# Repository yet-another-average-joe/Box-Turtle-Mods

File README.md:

# Box-Turtle-Mods
Box Turtle mods based on 78mm-wide trays

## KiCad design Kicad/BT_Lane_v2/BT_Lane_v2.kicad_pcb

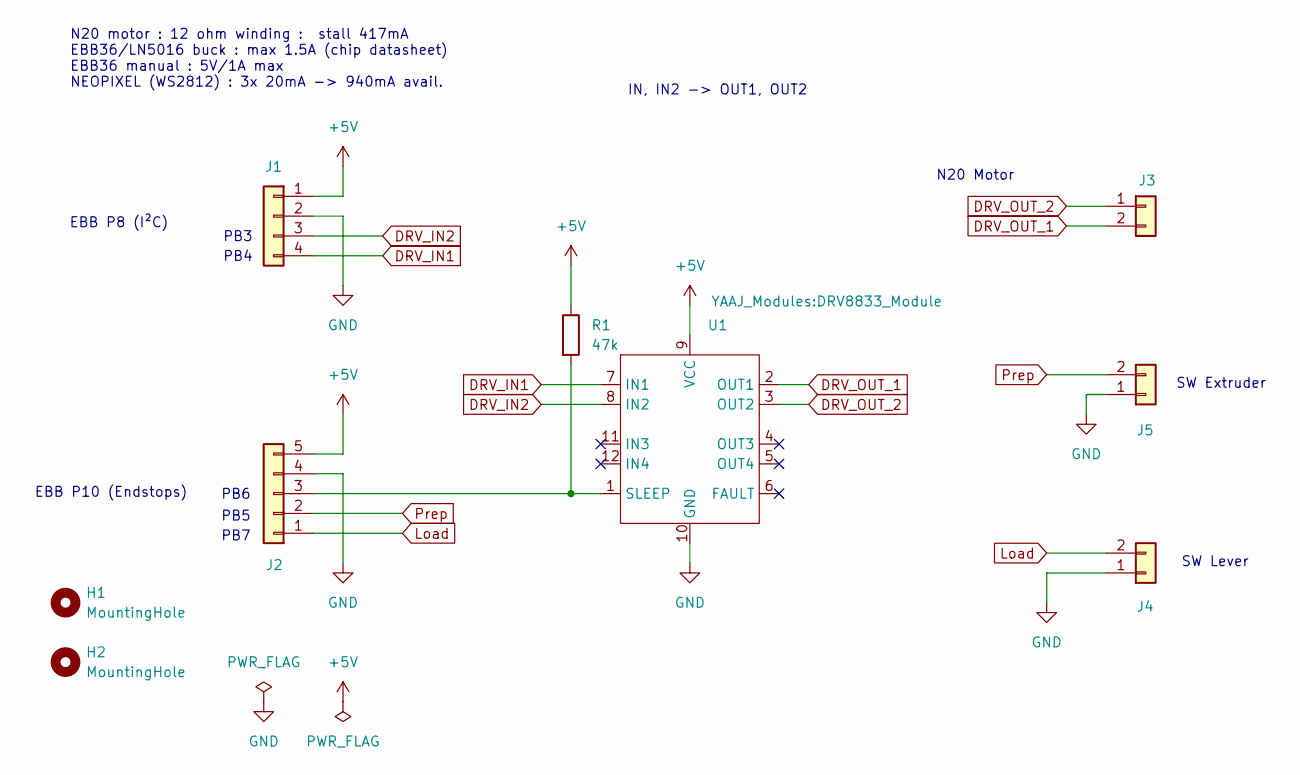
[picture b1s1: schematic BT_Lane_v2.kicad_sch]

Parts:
H1, H2: MountingHole; MountingHole_3.5mm_Pad_Via
J1: Conn_01x04; JST_XH_B4B-XH-A_1x04_P2.50mm_Vertical
J2: Conn_01x05; JST_XH_B5B-XH-A_1x05_P2.50mm_Vertical
J3, J4, J5: Conn_01x02; JST_XH_B2B-XH-A_1x02_P2.50mm_Vertical
R1: 47k; R_Axial_DIN0204_L3.6mm_D1.6mm_P1.90mm_Vertical
U1: DRV8833_Module

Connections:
+5V: J1.1, J2.5, R1.1, U1.9 (VCC)
DRV_IN1: J1.4, U1.7 (IN1)
DRV_IN2: J1.3, U1.8 (IN2)
DRV_OUT_1: J3.2, U1.2 (OUT1)
DRV_OUT_2: J3.1, U1.3 (OUT2)
GND: J1.2, J2.4, J4.1, J5.1, U1.10 (GND)
Load: J2.1, J4.2
unnamed: J2.3, R1.2, U1.1 (SLEEP)
Prep: J2.2, J5.2

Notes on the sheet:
EBB P8 (I²C)
EBB P10 (Endstops)
SW Extruder
N20 motor : 12 ohm winding : stall 417mA EBB36/LN5016 buck : max 1.5A (chip datasheet) EBB36 manual : 5V/1A max NEOPIXEL (WS2812) : 3x 20mA -> 940mA avail.
SW Lever
N20 Motor
PB6
PB3
PB4
PB5
PB7
IN, IN2 -> OUT1, OUT2

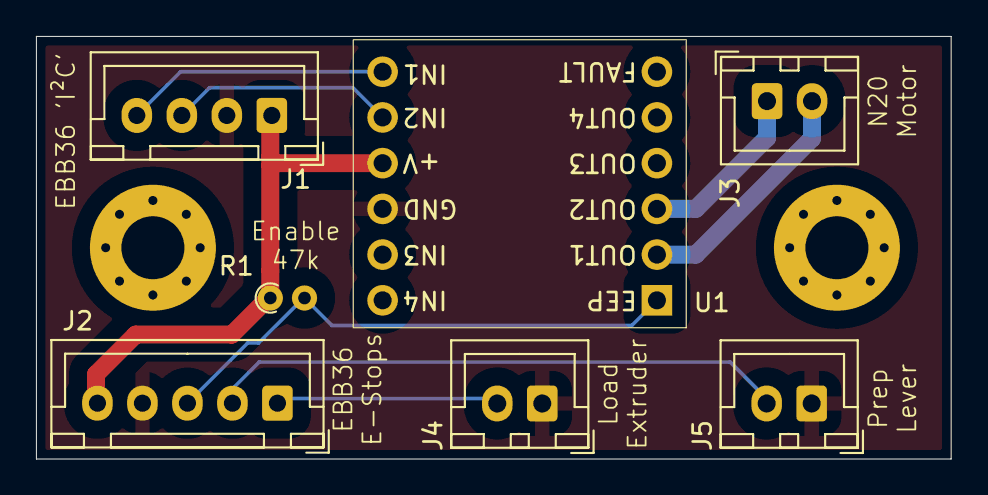
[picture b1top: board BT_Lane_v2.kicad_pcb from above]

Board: 2 copper layers, 50.8 x 23.5 mm, 9 parts (0 on the bottom side), 9 nets.
